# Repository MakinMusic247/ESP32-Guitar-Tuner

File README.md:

# ESP32-guitar-tuner
ESP32 Based guitar tuner

## Background
Each note played on the guitar creates a signal with a certain fundamental frequency

We can determine the note being played by working out the fundamental frequency of the signal taken from the guitar

## Circuit board
The signal coming from an electric guitar is small (approximately +-100->300mV). For a microcontoller to distinguish between samples of similar magnitude, we should amplify the signal to maximize these differences. A typical microcontroller accepts voltages in the range of 0-3.3V or 0.5V, and the analog pins can be damaged by the negative part of an incoming AC signal. 

From the simulation results below we can see that the circuit can offset and amplify the incoming signal to fit the desired range of the microcontroller analog pin (green is the input guitar signal and blue is the output of the amplifier/offset circuit)

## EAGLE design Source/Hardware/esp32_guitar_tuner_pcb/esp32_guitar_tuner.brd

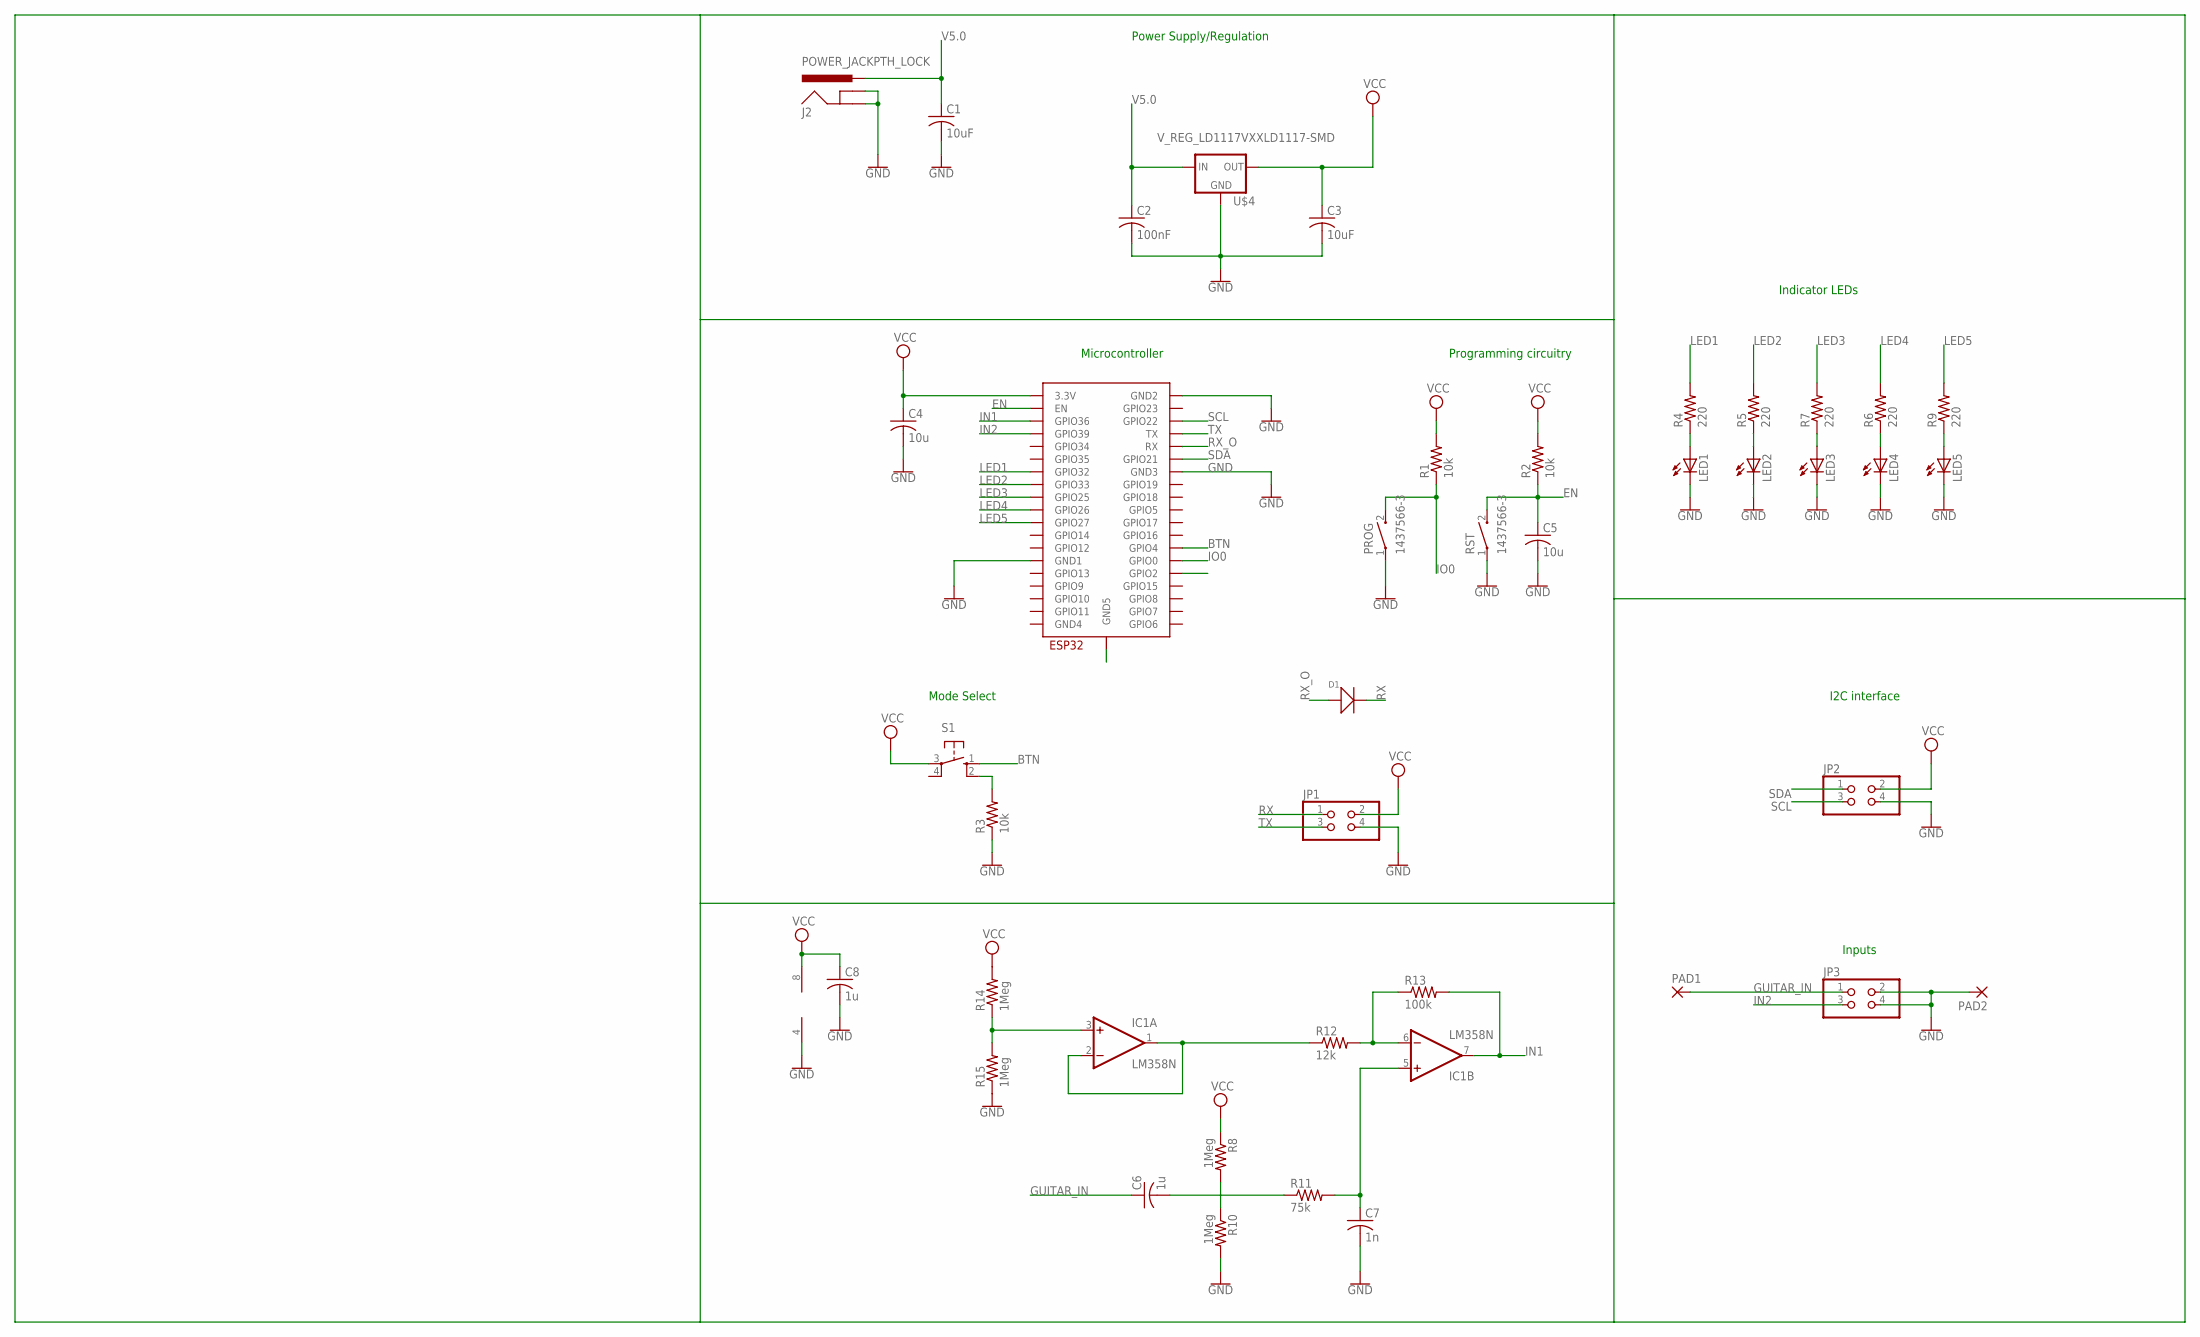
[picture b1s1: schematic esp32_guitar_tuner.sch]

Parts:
C1, C3: 10uF; C0805
C2: 100nF; C0805
C4, C5: 10u; C0805
C6, C8: 1u; C0805
C7: 1n; C0805
D1: DIODE'0805'; SOD-323
IC1: LM358N; DIL08
J2: POWER_JACKPTH_LOCK; POWER_JACK_PTH_LOCK
JP1, JP2, JP3: PINHD-2X2; 2X02
LED1, LED2, LED3, LED4, LED5: LEDCHIPLED_0805; CHIPLED_0805
PAD1, PAD2: SMD5; SMD2,54-5,08
PROG: 1437566-3; SW_1437566-3
R1, R2, R3: 10k; R0805
R4, R5, R6, R7, R9: 220; R0805
R8, R10, R14, R15: 1Meg; R0805
R11: 75k; R0805
R12: 12k; R0805
R13: 100k; R0805
RST: 1437566-3; SW_1437566-3
S1: 10-XX; B3F-10XX
U$1: ESP32-WROOM
U$4: V_REG_LD1117VXXLD1117-SMD; SOT223

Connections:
ALARM: U$1.IO2 (GPIO2)
BTN: S1.1 (S), U$1.IO4 (GPIO4)
EN: C5.1, R2.1, RST.2, U$1.EN
GND: C1.2, C2.2, C3.2, C4.2, C5.2, C7.2, C8.2, IC1.4 (V-), J2.GND, J2.GNDBREAK, JP1.4, JP2.4, JP3.2, JP3.4, LED1.C, LED2.C, LED3.C, LED4.C, LED5.C, PAD2.1, PROG.1, R3.1, R10.2, R15.1, RST.1, U$1.GND1, U$1.GND2, U$1.GND3, U$4.1 (GND)
GUITAR_IN: C6.1, JP3.1, PAD1.1
IN1: IC1.7 (OUT), R13.2, U$1.SENSOR_VP (GPIO36)
IN2: JP3.3, U$1.SENSOR_VN (GPIO39)
IO0: PROG.2, R1.1, U$1.IO0 (GPIO0)
LED1: R4.2, U$1.IO32 (GPIO32)
LED2: R5.2, U$1.IO33 (GPIO33)
LED3: R7.2, U$1.IO25 (GPIO25)
LED4: R6.2, U$1.IO26 (GPIO26)
LED5: R9.2, U$1.IO27 (GPIO27)
unnamed: R3.2, S1.2 (S1)
unnamed: LED2.A, R5.1
unnamed: LED4.A, R6.1
unnamed: LED1.A, R4.1
unnamed: LED3.A, R7.1
unnamed: C6.2, R11.1
unnamed: LED5.A, R9.1
unnamed: R8.2, R10.1
unnamed: C7.1, IC1.5 (+IN), R11.2
unnamed: IC1.6 (-IN), R12.2, R13.1
unnamed: IC1.1 (OUT), IC1.2 (-IN), R12.1
unnamed: IC1.3 (+IN), R14.1, R15.2
RX: D1.-, JP1.1
RX_O: D1.+, U$1.RX
SCL: JP2.3, U$1.IO22 (GPIO22)
SDA: JP2.1, U$1.IO21 (GPIO21)
TX: JP1.3, U$1.TX
V5.0: C1.1, C2.1, J2.PWR, U$4.3 (IN)
VCC: C3.1, C4.1, C8.1, IC1.8 (V+), JP1.2, JP2.2, R1.2, R2.2, R8.1, R14.2, S1.3, U$1.3V3 (3.3V), U$4.2 (OUT)

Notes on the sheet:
Microcontroller
Power Supply/Regulation
Programming circuitry
Indicator LEDs
Mode Select
I2C interface
Inputs

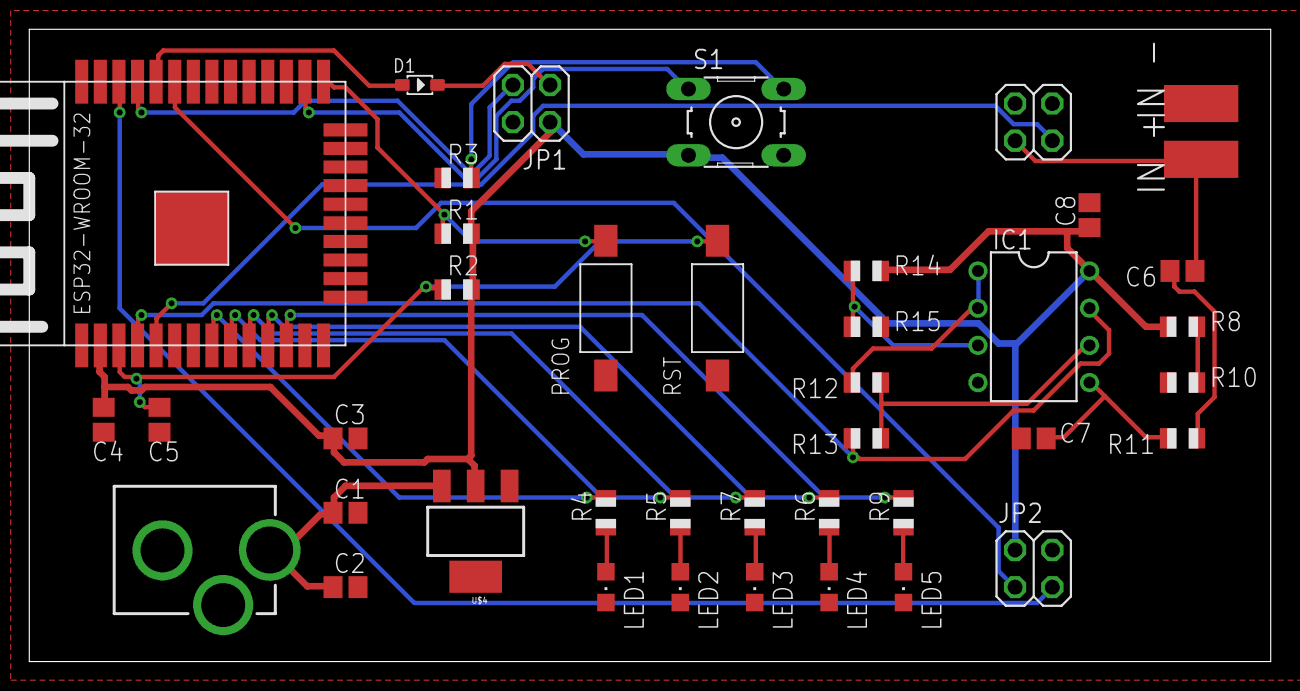
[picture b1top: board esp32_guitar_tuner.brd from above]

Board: 2 copper layers, 84.8 x 43.2 mm, 41 parts (0 on the bottom side), 31 nets.

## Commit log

2022-04-04 update firmware

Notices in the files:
parts and their libraries:
SparkFun-Connectors: Licensing: Creative Commons ShareAlike 4.0 International - https://creativecommons.org/licenses/by-sa/4.0
